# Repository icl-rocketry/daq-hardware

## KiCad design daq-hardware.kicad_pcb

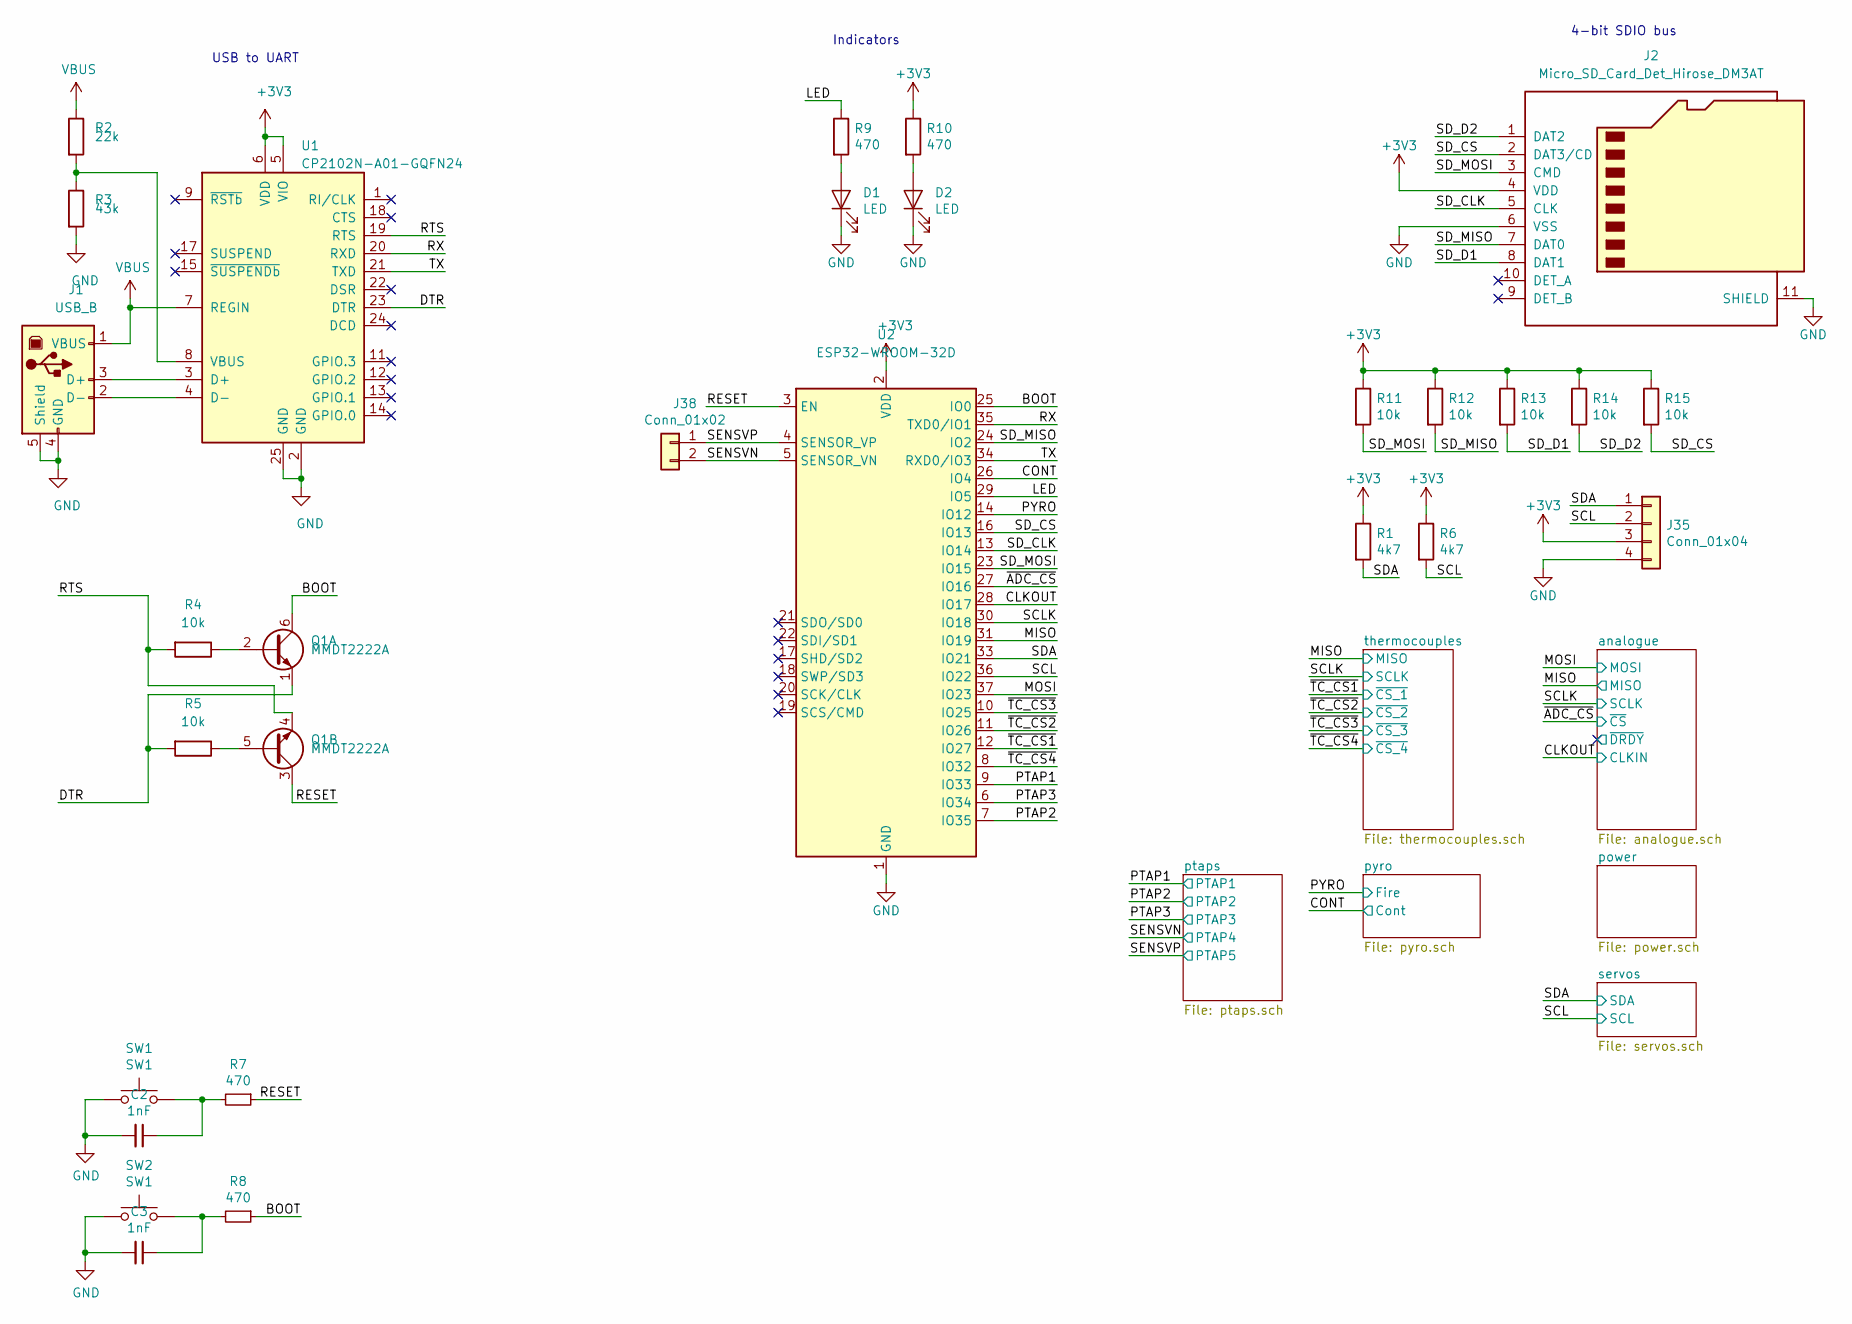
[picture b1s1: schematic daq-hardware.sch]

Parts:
C2, C3: 1nF; C_0603_1608Metric
D1, D2: LED; LED_0603_1608Metric_Castellated
J1: USB_B; USB_B_OST_USB-B1HSxx_Horizontal
J2: Micro_SD_Card_Det_Hirose_DM3AT; microSD_HC_Hirose_DM3AT-SF-PEJM5
J35: Conn_01x04; PinHeader_1x04_P2.54mm_Vertical
J38: Conn_01x02; PinHeader_1x02_P2.54mm_Vertical
Q1: MMDT2222A; SOT-363_SC-70-6
R1, R6: 4k7; R_0603_1608Metric
R2: 22k; R_0603_1608Metric
R3: 43k; R_0603_1608Metric
R4, R5, R11, R12, R13, R14, R15: 10k; R_0603_1608Metric
R7, R8, R9, R10: 470; R_0603_1608Metric
SW1, SW2: SW1; SW_Push_1P1T_NO_CK_KMR2
U1: CP2102N-A01-GQFN24; QFN-24-1EP_4x4mm_P0.5mm_EP2.6x2.6mm_ThermalVias
U2: ESP32-WROOM-32D; ESP32-WROOM-32U

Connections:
+3V3: J2.4 (VDD), J35.3, R1.1, R6.1, R10.1, R11.1, R12.1, R13.1, R14.1, R15.1, U1.5 (VIO), U1.6 (VDD), U2.2 (VDD); also elsewhere on the board
/BOOT: Q1.6 (C1), R8.1, U2.25 (IO0); also elsewhere on the board
/CLKOUT: U2.28 (IO17); also elsewhere on the board
/CONT: U2.26 (IO4); also elsewhere on the board
/DTR: Q1.1 (E1), R5.2, U1.23 (DTR)
/LED: R9.1, U2.29 (IO5); also elsewhere on the board
/MISO: U2.31 (IO19); also elsewhere on the board
/MOSI: U2.37 (IO23); also elsewhere on the board
/PTAP1: U2.9 (IO33); also elsewhere on the board
/PTAP2: U2.7 (IO35); also elsewhere on the board
/PTAP3: U2.6 (IO34); also elsewhere on the board
/PYRO: U2.14 (IO12); also elsewhere on the board
/RESET: Q1.3 (C2), R7.1, U2.3 (EN); also elsewhere on the board
/RTS: Q1.4 (E2), R4.2, U1.19 (RTS)
/RX: U1.20 (RXD), U2.35 (TXD0/IO1); also elsewhere on the board
/SCL: J35.2, R6.2, U2.36 (IO22); also elsewhere on the board
/SCLK: U2.30 (IO18); also elsewhere on the board
/SDA: J35.1, R1.2, U2.33 (IO21); also elsewhere on the board
/SD_CLK: J2.5 (CLK), U2.13 (IO14); also elsewhere on the board
/SD_CS: J2.2 (DAT3/CD), R15.2, U2.16 (IO13); also elsewhere on the board
/SD_D1: J2.8 (DAT1), R13.2
/SD_D2: J2.1 (DAT2), R14.2
/SD_MISO: J2.7 (DAT0), R12.2, U2.24 (IO2); also elsewhere on the board
/SD_MOSI: J2.3 (CMD), R11.2, U2.23 (IO15); also elsewhere on the board
/SENSVN: J38.2, U2.5 (SENSOR_VN); also elsewhere on the board
/SENSVP: J38.1, U2.4 (SENSOR_VP); also elsewhere on the board
/TX: U1.21 (TXD), U2.34 (RXD0/IO3); also elsewhere on the board
/~ADC_CS: U2.27 (IO16); also elsewhere on the board
/~TC_CS1: U2.12 (IO27); also elsewhere on the board
/~TC_CS2: U2.11 (IO26); also elsewhere on the board
/~TC_CS3: U2.10 (IO25); also elsewhere on the board
/~TC_CS4: U2.8 (IO32); also elsewhere on the board
GND: C2.2, C3.2, D1.1 (K), D2.1 (K), J1.4 (GND), J1.5 (Shield), J2.6 (VSS), J2.11 (SHIELD), J35.4, R3.2, SW1.1, SW2.1, U1.2 (GND), U1.25 (GND), U2.1 (GND), U2.15 (GND), U2.38 (GND); also elsewhere on the board
unnamed: C2.1, R7.2, SW1.2
unnamed: C3.1, R8.2, SW2.2
unnamed: D1.2 (A), R9.2
unnamed: D2.2 (A), R10.2
unnamed: J1.2 (D-), U1.4 (D-)
unnamed: J1.3 (D+), U1.3 (D+)
unnamed: Q1.2 (B1), R4.1
unnamed: Q1.5 (B2), R5.1
unnamed: R2.2, R3.1, U1.8 (VBUS)
unnamed 113: U2.17 (SHD/SD2); also elsewhere on the board
unnamed 114: U2.18 (SWP/SD3); also elsewhere on the board
unnamed 115: U2.19 (SCS/CMD); also elsewhere on the board
unnamed 116: U2.20 (SCK/CLK); also elsewhere on the board
unnamed 117: U2.21 (SDO/SD0); also elsewhere on the board
unnamed 118: U2.22 (SDI/SD1); also elsewhere on the board
unnamed 119: U2.32 (NC); also elsewhere on the board
VBUS: J1.1 (VBUS), R2.1, U1.7 (REGIN); also elsewhere on the board

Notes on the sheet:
4-bit SDIO bus
USB to UART
Indicators

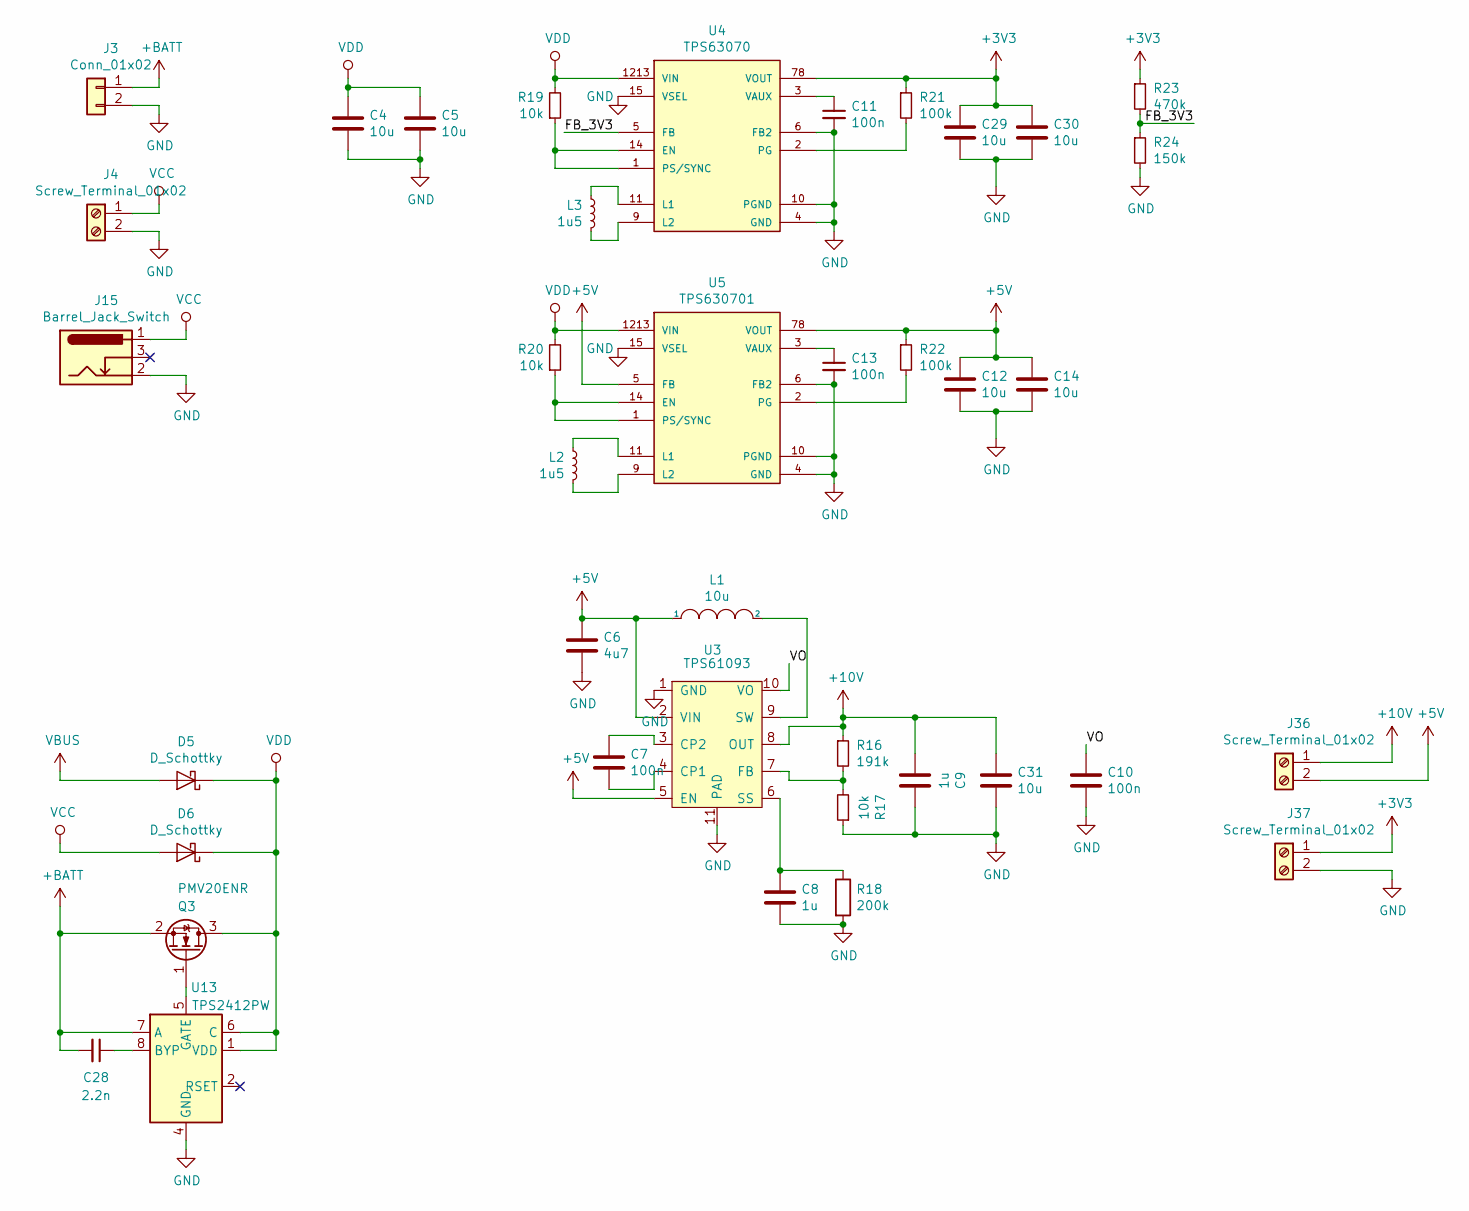
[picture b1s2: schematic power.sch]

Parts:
C4, C5, C12, C14, C29, C30, C31: 10u; CP_Elec_4x5.4
C6: 4u7; C_0603_1608Metric
C7, C10, C11, C13: 100n; C_0603_1608Metric
C8, C9: 1u; C_0603_1608Metric
C28: 2.2n; C_0603_1608Metric
D5, D6: D_Schottky; D_SOD-123F
J3: Conn_01x02; JST_PH_S2B-PH-K_1x02_P2.00mm_Horizontal
J4, J36, J37: Screw_Terminal_01x02; TerminalBlock_Phoenix_MPT-2.54mm_2pol
J15: Barrel_Jack_Switch; BarrelJack_Wuerth_6941xx301002
L1: 10u; L_Taiyo-Yuden_NR-30xx
L2, L3: 1u5; L_Taiyo-Yuden_NR-30xx
Q3: PMV20ENR; SOT-23
R16: 191k; R_0603_1608Metric
R17, R19, R20: 10k; R_0603_1608Metric
R18: 200k; R_0603_1608Metric
R21, R22: 100k; R_0603_1608Metric
R23: 470k; R_0603_1608Metric
R24: 150k; R_0603_1608Metric
U3: TPS61093; Texas_S-PWSON-N10_ThermalVias
U4: TPS63070; Texas_PowerVFQFN_15
U5: TPS630701; Texas_PowerVFQFN_15
U13: TPS2412PW; TSSOP-8_4.4x3mm_P0.65mm

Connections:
+3V3: C29.1, C30.1, J37.1, R21.1, R23.1, U4.78 (VOUT); also elsewhere on the board
+5V: C6.1, C12.1, C14.1, J36.2, L1.1, R22.1, U3.2 (VIN), U3.5 (EN), U5.5 (FB), U5.78 (VOUT); also elsewhere on the board
+10V: C9.2, C31.1, J36.1, R16.1, U3.8 (OUT)
+BATT: C28.2, J3.1, Q3.2 (S), U13.7 (A)
/power/FB_3V3: R23.2, R24.1, U4.5 (FB)
/power/VO: C10.1, U3.10 (VO)
GND: C4.2, C5.2, C6.2, C8.2, C9.1, C10.2, C11.2, C12.2, C13.2, C14.2, C29.2, C30.2, C31.2, J3.2, J4.2, J15.2, J37.2, R17.1, R18.2, R24.2, U3.1 (GND), U3.11 (PAD), U4.4 (GND), U4.6 (FB2), U4.10 (PGND), U4.15 (VSEL), U5.4 (GND), U5.6 (FB2), U5.10 (PGND), U5.15 (VSEL), U13.3 (GND), U13.4 (GND); also elsewhere on the board
unnamed: C7.1, U3.3 (CP2)
unnamed: C7.2, U3.4 (CP1)
unnamed: C8.1, R18.1, U3.6 (SS)
unnamed: C11.1, U4.3 (VAUX)
unnamed: C13.1, U5.3 (VAUX)
unnamed: C28.1, U13.8 (BYP)
unnamed: L1.2, U3.9 (SW)
unnamed: L2.1, U5.9 (L2)
unnamed: L2.2, U5.11 (L1)
unnamed: L3.1, U4.9 (L2)
unnamed: L3.2, U4.11 (L1)
unnamed: Q3.1 (G), U13.5 (GATE)
unnamed: R16.2, R17.2, U3.7 (FB)
unnamed: R19.1, U4.1 (PS/SYNC), U4.14 (EN)
unnamed: R20.1, U5.1 (PS/SYNC), U5.14 (EN)
unnamed: R21.2, U4.2 (PG)
unnamed: R22.2, U5.2 (PG)
VBUS: D5.2 (A); also elsewhere on the board
VCC: D6.2 (A), J4.1, J15.1
VDD: C4.1, C5.1, D5.1 (K), D6.1 (K), Q3.3 (D), R19.2, R20.2, U4.1213 (VIN), U5.1213 (VIN), U13.1 (VDD), U13.6 (C)

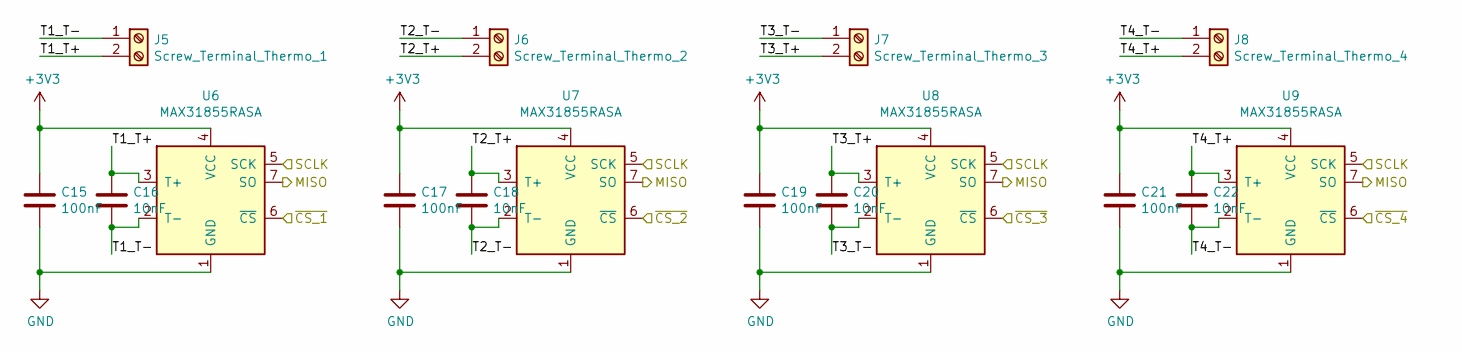
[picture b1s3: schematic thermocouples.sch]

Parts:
C15, C17, C19, C21: 100nF; C_0603_1608Metric
C16, C18, C20, C22: 10nF; C_0603_1608Metric
J5: Screw_Terminal_Thermo_1; TerminalBlock_Phoenix_MPT-2.54mm_2pol
J6: Screw_Terminal_Thermo_2; TerminalBlock_Phoenix_MPT-2.54mm_2pol
J7: Screw_Terminal_Thermo_3; TerminalBlock_Phoenix_MPT-2.54mm_2pol
J8: Screw_Terminal_Thermo_4; TerminalBlock_Phoenix_MPT-2.54mm_2pol
U6, U7, U8, U9: MAX31855RASA; SOIC-8_3.9x4.9mm_P1.27mm

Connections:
+3V3: C15.1, C17.1, C19.1, C21.1, U6.4 (VCC), U7.4 (VCC), U8.4 (VCC), U9.4 (VCC); also elsewhere on the board
/MISO: U6.7 (SO), U7.7 (SO), U8.7 (SO), U9.7 (SO); also elsewhere on the board
/SCLK: U6.5 (SCK), U7.5 (SCK), U8.5 (SCK), U9.5 (SCK); also elsewhere on the board
/thermocouples/T1_T+: C16.1, J5.2, U6.3 (T+)
/thermocouples/T1_T-: C16.2, J5.1, U6.2 (T-)
/thermocouples/T2_T+: C18.1, J6.2, U7.3 (T+)
/thermocouples/T2_T-: C18.2, J6.1, U7.2 (T-)
/thermocouples/T3_T+: C20.1, J7.2, U8.3 (T+)
/thermocouples/T3_T-: C20.2, J7.1, U8.2 (T-)
/thermocouples/T4_T+: C22.1, J8.2, U9.3 (T+)
/thermocouples/T4_T-: C22.2, J8.1, U9.2 (T-)
/~TC_CS1: U6.6 (~CS~); also elsewhere on the board
/~TC_CS2: U7.6 (~CS~); also elsewhere on the board
/~TC_CS3: U8.6 (~CS~); also elsewhere on the board
/~TC_CS4: U9.6 (~CS~); also elsewhere on the board
GND: C15.2, C17.2, C19.2, C21.2, U6.1 (GND), U7.1 (GND), U8.1 (GND), U9.1 (GND); also elsewhere on the board

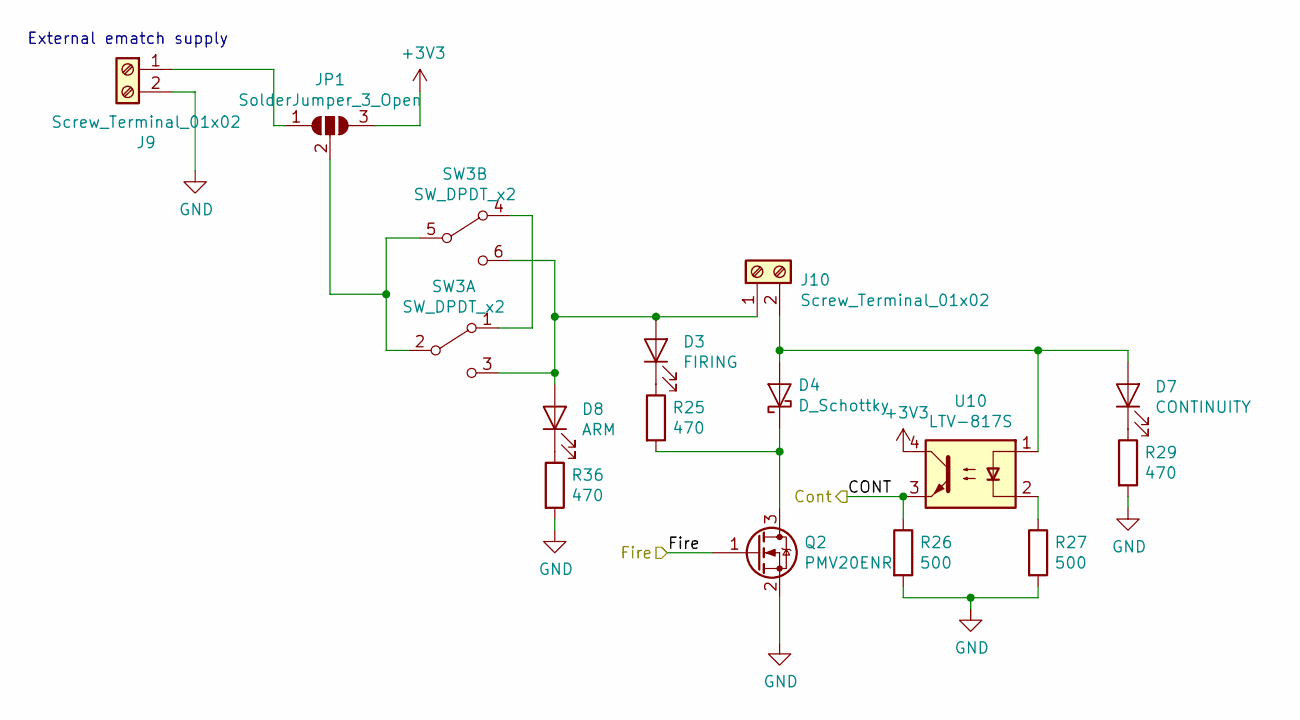
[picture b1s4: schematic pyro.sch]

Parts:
D3: FIRING; LED_0603_1608Metric_Castellated
D4: D_Schottky; D_SOD-123F
D7: CONTINUITY; LED_0603_1608Metric_Castellated
D8: ARM; LED_0603_1608Metric_Castellated
J9, J10: Screw_Terminal_01x02; TerminalBlock_Phoenix_MPT-0,5-2-2.54_1x02_P2.54mm_Horizontal
JP1: SolderJumper_3_Open; SolderJumper-3_P1.3mm_Open_RoundedPad1.0x1.5mm_NumberLabels
Q2: PMV20ENR; SOT-23
R25, R29, R36: 470; R_0603_1608Metric
R26, R27: 500; R_0603_1608Metric
SW3: SW_DPDT_x2; SW_CuK_JS202011AQN_DPDT_Angled
U10: LTV-817S; SMDIP-4_W9.53mm

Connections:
+3V3: JP1.3 (B), U10.4; also elsewhere on the board
/CONT: R26.1, U10.3; also elsewhere on the board
/PYRO: Q2.1 (G); also elsewhere on the board
GND: J9.2, Q2.2 (S), R26.2, R27.2, R29.2, R36.2; also elsewhere on the board
unnamed: D3.1 (K), R25.1
unnamed: D3.2 (A), D8.2 (A), J10.1, SW3.3 (C), SW3.6 (C)
unnamed: D4.1 (K), Q2.3 (D), R25.2
unnamed: D4.2 (A), D7.2 (A), J10.2, U10.1
unnamed: D7.1 (K), R29.1
unnamed: D8.1 (K), R36.1
unnamed: J9.1, JP1.1 (A)
unnamed: JP1.2 (C), SW3.2 (B), SW3.5 (B)
unnamed: R27.1, U10.2
unnamed: SW3.1 (A), SW3.4 (A)

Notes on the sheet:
External ematch supply

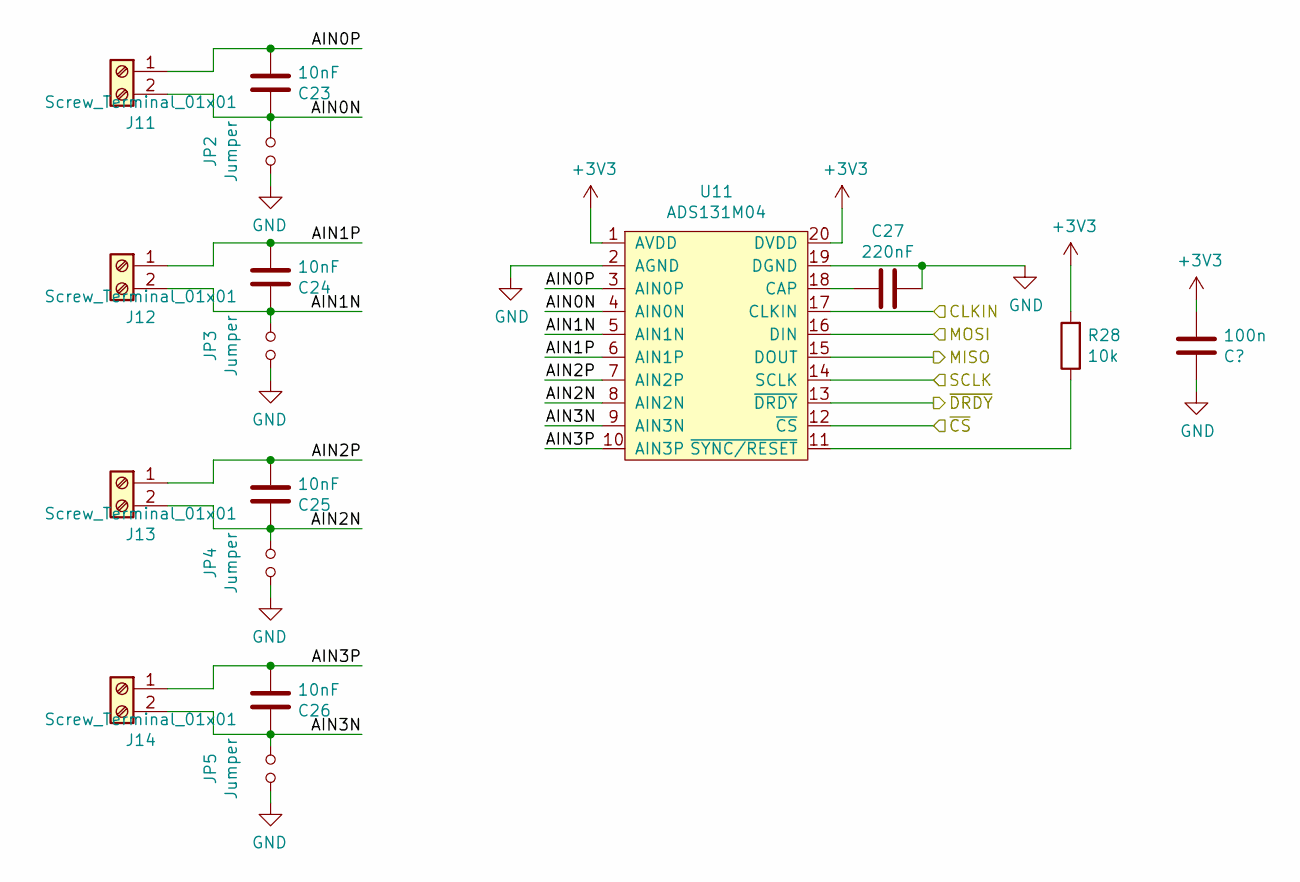
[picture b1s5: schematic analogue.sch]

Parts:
C23, C24, C25, C26: 10nF; C_0603_1608Metric
C27: 220nF; C_0603_1608Metric_Pad1.05x0.95mm_HandSolder
J11, J12, J13, J14: Screw_Terminal_01x01; TerminalBlock_Phoenix_MPT-2.54mm_2pol
JP2, JP3, JP4, JP5: Jumper; PinHeader_1x02_P2.54mm_Vertical
R28: 10k; R_0603_1608Metric
U11: ADS131M04; TSSOP-20_4.4x6.5mm_Pitch0.65mm

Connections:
+3V3: R28.2, U11.1 (AVDD), U11.20 (DVDD); also elsewhere on the board
/CLKOUT: U11.17 (CLKIN); also elsewhere on the board
/MISO: U11.15 (DOUT); also elsewhere on the board
/MOSI: U11.16 (DIN); also elsewhere on the board
/SCLK: U11.14 (SCLK); also elsewhere on the board
/analogue/AIN0N: C23.1, J11.2, JP2.1, U11.4 (AIN0N)
/analogue/AIN0P: C23.2, J11.1, U11.3 (AIN0P)
/analogue/AIN1N: C24.1, J12.2, JP3.1, U11.5 (AIN1N)
/analogue/AIN1P: C24.2, J12.1, U11.6 (AIN1P)
/analogue/AIN2N: C25.1, J13.2, JP4.1, U11.8 (AIN2N)
/analogue/AIN2P: C25.2, J13.1, U11.7 (AIN2P)
/analogue/AIN3N: C26.1, J14.2, JP5.1, U11.9 (AIN3N)
/analogue/AIN3P: C26.2, J14.1, U11.10 (AIN3P)
/~ADC_CS: U11.12 (~CS); also elsewhere on the board
GND: C27.1, JP2.2, JP3.2, JP4.2, JP5.2, U11.2 (AGND), U11.19 (DGND); also elsewhere on the board
unnamed: C27.2, U11.18 (CAP)
unnamed: R28.1, U11.11 (~SYNC/RESET)

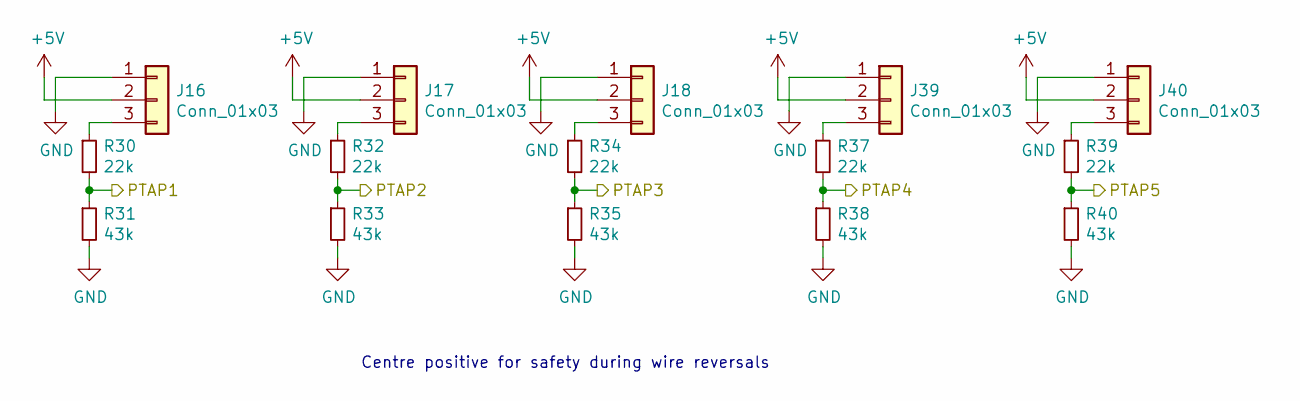
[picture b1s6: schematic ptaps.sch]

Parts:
J16, J17, J18, J39, J40: Conn_01x03; JST_XH_B3B-XH-A_1x03_P2.50mm_Vertical
R30, R32, R34, R37, R39: 22k; R_0603_1608Metric
R31, R33, R35, R38, R40: 43k; R_0603_1608Metric

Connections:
+5V: J16.2, J17.2, J18.2, J39.2, J40.2; also elsewhere on the board
/PTAP1: R30.2, R31.1; also elsewhere on the board
/PTAP2: R32.2, R33.1; also elsewhere on the board
/PTAP3: R34.2, R35.1; also elsewhere on the board
/SENSVN: R37.2, R38.1; also elsewhere on the board
/SENSVP: R39.2, R40.1; also elsewhere on the board
GND: J16.1, J17.1, J18.1, J39.1, J40.1, R31.2, R33.2, R35.2, R38.2, R40.2; also elsewhere on the board
unnamed: J16.3, R30.1
unnamed: J17.3, R32.1
unnamed: J18.3, R34.1
unnamed: J39.3, R37.1
unnamed: J40.3, R39.1

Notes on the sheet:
Centre positive for safety during wire reversals

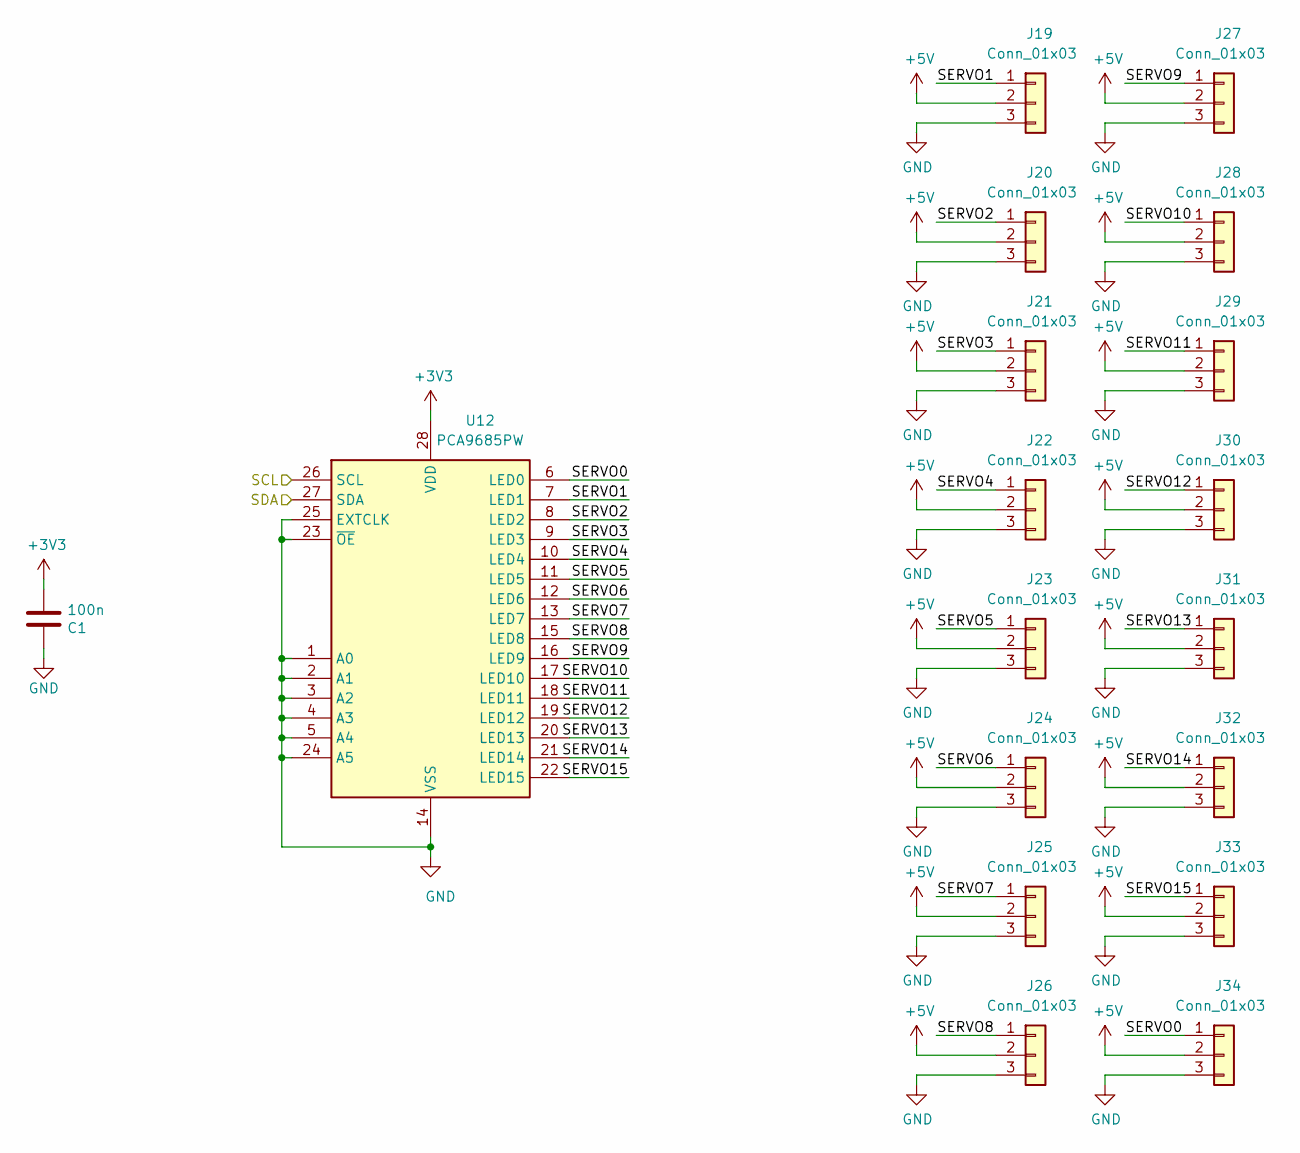
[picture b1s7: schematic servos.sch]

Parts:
C1: 100n; C_0603_1608Metric
J19, J20, J21, J22, J23, J24, J25, J26, J27, J28, J29, J30, J31, J32, J33, J34: Conn_01x03; PinHeader_1x03_P2.54mm_Vertical
U12: PCA9685PW; TSSOP-28_4.4x9.7mm_P0.65mm

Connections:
+3V3: C1.2, U12.28 (VDD); also elsewhere on the board
+5V: J19.2, J20.2, J21.2, J22.2, J23.2, J24.2, J25.2, J26.2, J27.2, J28.2, J29.2, J30.2, J31.2, J32.2, J33.2, J34.2; also elsewhere on the board
/SCL: U12.26 (SCL); also elsewhere on the board
/SDA: U12.27 (SDA); also elsewhere on the board
/servos/SERVO0: J34.1, U12.6 (LED0)
/servos/SERVO1: J19.1, U12.7 (LED1)
/servos/SERVO2: J20.1, U12.8 (LED2)
/servos/SERVO3: J21.1, U12.9 (LED3)
/servos/SERVO4: J22.1, U12.10 (LED4)
/servos/SERVO5: J23.1, U12.11 (LED5)
/servos/SERVO6: J24.1, U12.12 (LED6)
/servos/SERVO7: J25.1, U12.13 (LED7)
/servos/SERVO8: J26.1, U12.15 (LED8)
/servos/SERVO9: J27.1, U12.16 (LED9)
/servos/SERVO10: J28.1, U12.17 (LED10)
/servos/SERVO11: J29.1, U12.18 (LED11)
/servos/SERVO12: J30.1, U12.19 (LED12)
/servos/SERVO13: J31.1, U12.20 (LED13)
/servos/SERVO14: J32.1, U12.21 (LED14)
/servos/SERVO15: J33.1, U12.22 (LED15)
GND: C1.1, J19.3, J20.3, J21.3, J22.3, J23.3, J24.3, J25.3, J26.3, J27.3, J28.3, J29.3, J30.3, J31.3, J32.3, J33.3, J34.3, U12.1 (A0), U12.2 (A1), U12.3 (A2), U12.4 (A3), U12.5 (A4), U12.14 (VSS), U12.23 (~OE), U12.24 (A5), U12.25 (EXTCLK); also elsewhere on the board

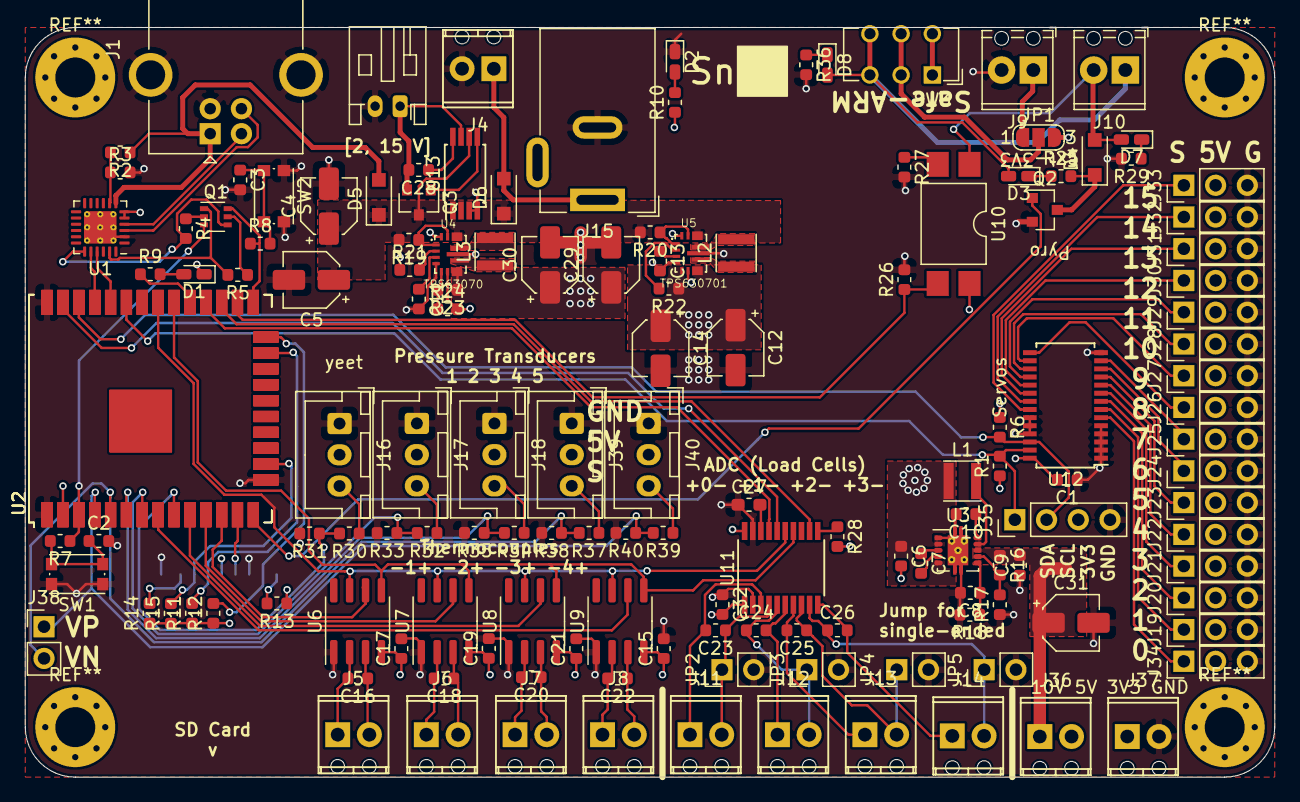
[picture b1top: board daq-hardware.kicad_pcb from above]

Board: 4 copper layers, 100.0 x 60.0 mm, 149 parts (1 on the bottom side), 123 nets.

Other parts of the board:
C32: 100n; C_0603_1608Metric
U2#2, U2#3: ESP32-WROOM-32D; ESP32-WROOM-32U

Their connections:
+3V3: C32.2, U2#2.2, U2#3.2; also elsewhere on the board
/BOOT: U2#2.25, U2#3.25; also elsewhere on the board
/CLKOUT: U2#2.28, U2#3.28; also elsewhere on the board
/CONT: U2#2.26, U2#3.26; also elsewhere on the board
/LED: U2#2.29, U2#3.29; also elsewhere on the board
/MISO: U2#2.31, U2#3.31; also elsewhere on the board
/MOSI: U2#2.37, U2#3.37; also elsewhere on the board
/PTAP1: U2#2.9, U2#3.9; also elsewhere on the board
/PTAP2: U2#2.7, U2#3.7; also elsewhere on the board
/PTAP3: U2#2.6, U2#3.6; also elsewhere on the board
/PYRO: U2#2.14, U2#3.14; also elsewhere on the board
/RESET: U2#2.3, U2#3.3; also elsewhere on the board
/RX: U2#2.35, U2#3.35; also elsewhere on the board
/SCL: U2#2.36, U2#3.36; also elsewhere on the board
/SCLK: U2#2.30, U2#3.30; also elsewhere on the board
/SDA: U2#2.33, U2#3.33; also elsewhere on the board
/SD_CLK: U2#2.13, U2#3.13; also elsewhere on the board
/SD_CS: U2#2.16, U2#3.16; also elsewhere on the board
/SD_MISO: U2#2.24, U2#3.24; also elsewhere on the board
/SD_MOSI: U2#2.23, U2#3.23; also elsewhere on the board
/SENSVN: U2#2.5, U2#3.5; also elsewhere on the board
/SENSVP: U2#2.4, U2#3.4; also elsewhere on the board
/TX: U2#2.34, U2#3.34; also elsewhere on the board
/~ADC_CS: U2#2.27, U2#3.27; also elsewhere on the board
/~TC_CS1: U2#2.12, U2#3.12; also elsewhere on the board
/~TC_CS2: U2#2.11, U2#3.11; also elsewhere on the board
/~TC_CS3: U2#2.10, U2#3.10; also elsewhere on the board
/~TC_CS4: U2#2.8, U2#3.8; also elsewhere on the board
GND: C32.1, U2#2.1, U2#2.15, U2#2.38, U2#3.1, U2#3.15, U2#3.38; also elsewhere on the board
unnamed 113: U2#2.17, U2#3.17; also elsewhere on the board
unnamed 114: U2#2.18, U2#3.18; also elsewhere on the board
unnamed 115: U2#2.19, U2#3.19; also elsewhere on the board
unnamed 116: U2#2.20, U2#3.20; also elsewhere on the board
unnamed 117: U2#2.21, U2#3.21; also elsewhere on the board
unnamed 118: U2#2.22, U2#3.22; also elsewhere on the board
unnamed 119: U2#2.32, U2#3.32; also elsewhere on the board

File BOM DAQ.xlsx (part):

Id | Designator | Package | Quantity | Designation | Supplier and ref | Digikey Part Nr | Unit Pricing | url
1 | C32,C13,C11,C1,C10,C7 | C_0603_1608Metric | 6 | 100n | Samsung Electro-Mech - CL10B104KB8NNNC | 1276-1000-1-ND | $0.02600 @ qty 10 | https://www.digikey.com/product-detail/en/samsung-electro-me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
2 | J40,J39,J18,J17,J16 | JST_XH_B3B-XH-A_1x03_P2.50mm_Vertical | 5 | Conn_01x03
3 | R40,R38,R35,R33,R31,R3 | R_0603_1608Metric | 6 | 43k | Yageo - RC0603FR-0743KL | 311-43.0KHRCT-ND | 0.1 | https://www.digikey.com/product-detail/en/yageo/RC0603FR-074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
4 | R39,R37,R34,R32,R30,R2 | R_0603_1608Metric | 6 | 22k | TE - CRGCQ0603F22K | A129704CT-ND | 0.1 | https://www.digikey.com/product-detail/en/te-connectivity-pa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
5 | J38 | PinHeader_1x02_P2.54mm_Vertical | 1 | Conn_01x02
6 | D2,D1 | LED_0603_1608Metric_Castellated | 2 | LED
7 | R36,R29,R10,R9,R8,R7,R25 | R_0603_1608Metric | 7 | 470 | TE - CRGCQ0603F470R | A129684CT-ND | 0.1 | https://www.digikey.com/product-detail/en/te-connectivity-pa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
8 | D8 | LED_0603_1608Metric_Castellated | 1 | ARM
9 | SW3 | SW_CuK_JS202011AQN_DPDT_Angled | 1 | SW_DPDT_x2 | C&K - JS202011AQN | 401-2000-ND | $0.43 | https://www.digikey.com/products/en?keywords=JS202011AQN
10 | C31,C30,C29,C14,C12,C5,C4 | CP_Elec_4x5.4 | 7 | 10u | Panasonic Elec - ECE-A1HKS100I | P19589CT-ND | $0.03400 @ qty 10 | https://www.digikey.com/product-detail/en/panasonic-electron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
11 | J37,J36,J4 | TerminalBlock_Phoenix_MPT-2.54mm_2pol | 3 | Screw_Terminal_01x02 | On Shore Tech - OSTVN02A150 | ED10561-ND | $0.91 | https://www.digikey.com/product-detail/en/on-shore-technolog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
12 | C27 | C_0603_1608Metric_Pad1.05x0.95mm_HandSolder | 1 | 220nF | Samsung Electro-Mech - CL10B222KB8NCNC | 1276-1989-1-ND | $0.02900 @ qty 10 | https://www.digikey.com/product-detail/en/samsung-electro-me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
13 | R20,R19,R12,R15,R14,R13,R11,R28,R17,R5,R4 | R_0603_1608Metric | 11 | 10k | TE -CRGCQ0603F10K | A129700CT-ND | 0.1 | https://www.digikey.com/product-detail/en/te-connectivity-pa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
14 | U4 | Texas_PowerVFQFN_15 | 1 | TPS63070 | Texas Instruments - TPS63070RNMR | 296-44874-1-ND | $2.67 | https://www.digikey.com/product-detail/en/texas-instruments/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
15 | R24 | R_0603_1608Metric | 1 | 150k | TE - CRGCQ0603F150K | A129714CT-ND | 0.1 | https://www.digikey.com/product-detail/en/te-connectivity-pa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
16 | R23 | R_0603_1608Metric | 1 | 470k | TE - CRGCQ0603F470K | A129720CT-ND | 0.1 | https://www.digikey.com/product-detail/en/te-connectivity-pa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
17 | U5 | Texas_PowerVFQFN_15 | 1 | TPS630701 | Texas Instruments - TPS630701RNMR | 296-47298-1-ND | $2.67 | https://www.digikey.com/product-detail/en/texas-instruments/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
18 | R22,R21 | R_0603_1608Metric | 2 | 100k | TE - CRGCQ0603F100K | A129712CT-ND | 0.1 | https://www.digikey.com/product-detail/en/te-connectivity-pa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
19 | L3,L2 | L_Taiyo-Yuden_NR-30xx | 2 | 1u5 | Taiyo Yuden - NR3015T1R5N | 587-2617-1-ND | $0.41 | https://www.digikey.com/product-detail/en/taiyo-yuden/NR3015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
20 | J35 | PinHeader_1x04_P2.54mm_Vertical | 1 | Conn_01x04
21 | JP3,JP5,JP4,JP2 | PinHeader_1x02_P2.54mm_Vertical | 4 | Jumper
22 | R6,R1 | R_0603_1608Metric | 2 | 4k7 | TE - CRGCQ0603F4K7 | A129696CT-ND | 0.1 | https://www.digikey.com/product-detail/en/te-connectivity-pa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
23 | J34,J33,J32,J31,J30,J29,J28,J27,J26,J25,J24,J23,J22,J21,J20,J19 | PinHeader_1x03_P2.54mm_Vertical | 16 | Conn_01x03
24 | U12 | TSSOP-28_4.4x9.7mm_P0.65mm | 1 | PCA9685PW | NXP USA - PCA9685PW,118 | 568-11925-1-ND | $2.33 | https://www.digikey.com/product-detail/en/nxp-usa-inc/PCA968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
25 | U2,U2,U2 | ESP32-WROOM-32U | 3 | ESP32-WROOM-32D | Expressif Systems - ESP32-WROOM-32D | 1904-1023-1-ND | $3.8 | https://www.digikey.com/product-detail/en/espressif-systems/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
26 | SW2,SW1 | SW_Push_1P1T_NO_CK_KMR2 | 2 | SW1 | C&K - K12SCS1.55NOLFTX | CKN10790CT-ND | $2.33 | https://www.digikey.com/product-detail/en/c-k/K12SCS1.55NOLF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
27 | D7 | LED_0603_1608Metric_Castellated | 1 | CONTINUITY
28 | D3 | LED_0603_1608Metric_Castellated | 1 | FIRING
29 | C3,C2 | C_0603_1608Metric | 2 | 1nF | Wurth - 885012206083 | 732-8001-1-ND | $0.01700 @ qty 10 | https://www.digikey.com/product-detail/en/w-rth-elektronik/8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
30 | D4,D6,D5 | D_SOD-123F | 3 | D_Schottky
31 | Q3,Q2 | SOT-23 | 2 | PMV20ENR | Nexperia USA - PMV20ENR | 1727-2301-1-ND | $0.39 | https://www.digikey.com/products/en/discrete-semiconductor-p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
32 | C28 | C_0603_1608Metric | 1 | 2.2n | Wurth - 885012206085 | 732-8003-1-ND | $0.01900 @ qty 10 | https://www.digikey.com/product-detail/en/w-rth-elektronik/8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
33 | U13 | TSSOP-8_4.4x3mm_P0.65mm | 1 | TPS2412PW | Texas Instruments - TPS2412PWR | 296-39371-1-ND | $2.88 | https://www.digikey.com/products/en/integrated-circuits-ics/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
34 | J15 | BarrelJack_Wuerth_6941xx301002 | 1 | Barrel_Jack_Switch
35 | J1 | USB_B_OST_USB-B1HSxx_Horizontal | 1 | USB_B | Kycon - KUSBX-SMTBS1NBTR | 2092-KUSBX-SMTBS1NBCT-ND | $1.50 | https://www.digikey.com/product-detail/en/kycon-inc/KUSBX-SM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
36 | JP1 | SolderJumper-3_P1.3mm_Open_RoundedPad1.0x1.5mm_NumberLabels | 1 | SolderJumper_3_Open
37 | J14,J13,J12,J11 | TerminalBlock_Phoenix_MPT-2.54mm_2pol | 4 | Screw_Terminal_01x01
38 | J8 | TerminalBlock_Phoenix_MPT-2.54mm_2pol | 1 | Screw_Terminal_Thermo_4
39 | J7 | TerminalBlock_Phoenix_MPT-2.54mm_2pol | 1 | Screw_Terminal_Thermo_3
40 | J6 | TerminalBlock_Phoenix_MPT-2.54mm_2pol | 1 | Screw_Terminal_Thermo_2
41 | J5 | TerminalBlock_Phoenix_MPT-2.54mm_2pol | 1 | Screw_Terminal_Thermo_1
42 | C15,C19,C17,C21 | C_0603_1608Metric | 4 | 100nF | Samsung Electro-Mech - CL10B104KB8NNNC | 1276-1000-1-ND | $0.02600 @ qty 10 | https://www.digikey.com/product-detail/en/samsung-electro-me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
43 | J2 | microSD_HC_Hirose_DM3AT-SF-PEJM5 | 1 | Micro_SD_Card_Det_Hirose_DM3AT | Hirose Electric Co Ltd - M3AT-SF-PEJM5 | HR1964CT-ND | $2.67 | https://www.digikey.com/product-detail/en/hirose-electric-co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
44 | U1 | QFN-24-1EP_4x4mm_P0.5mm_EP2.6x2.6mm_ThermalVias | 1 | CP2102N-A01-GQFN24 | Silicon Labs - CP2102N-A01-GQFN24R | 336-4737-1-ND | $1.35 | https://www.digikey.com/products/en/integrated-circuits-ics/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
45 | U11 | TSSOP-20_4.4x6.5mm_Pitch0.65mm | 1 | ADS131M04 | Texas Instruments - ADS131M04IPWT | 296-ADS131M04IPWTCT-ND | $6.22 | https://www.digikey.com/products/en/integrated-circuits-ics/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
46 | U3 | Texas_S-PWSON-N10_ThermalVias | 1 | TPS61093 | Texas Instruments - TPS61093DSKR | 296-39430-1-ND | $2.67 | https://www.digikey.com/product-detail/en/texas-instruments/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
47 | R18 | R_0603_1608Metric | 1 | 200k | Panasonic Electronics - ERJ-3EKF2003V | P200KHCT-ND | 0.1 | https://www.digikey.com/product-detail/en/panasonic-electron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
48 | R16 | R_0603_1608Metric | 1 | 191k | Panasonic Electronics - ERJ-3EKF1913V | P191KHCT-ND | 0.1 | https://www.digikey.com/product-detail/en/panasonic-electron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
49 | L1 | L_Taiyo-Yuden_NR-30xx | 1 | 10u | Taiyo Yuden - NR3015T100M | 587-1650-1-ND | $0.35 | https://www.digikey.com/product-detail/en/taiyo-yuden/NR3015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
50 | C26,C25,C24,C23,C22,C20,C18,C16 | C_0603_1608Metric | 8 | 10nF | Wurth - 885012206089 | 732-8007-1-ND | $0.01900 @ qty 10 | https://www.digikey.com/product-detail/en/w-rth-elektronik/8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
51 | C9,C8 | C_0603_1608Metric | 2 | 1u | Samsung Electro-Mech - CL10A105KQ8NNNC | 1276-1036-1-ND | $0.03300 @ qty 10 | https://www.digikey.com/product-detail/en/samsung-electro-me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
52 | C6 | C_0603_1608Metric | 1 | 4u7 | Samsung Electro-Mech - CL10A475KQ8NNNC | 1276-1045-1-ND | $0.05500 @ qty 10 | https://www.digikey.com/product-detail/en/samsung-electro-me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
53 | U10 | SMDIP-4_W9.53mm | 1 | LTV-817S | Lite-On LTV-817S-TA1 | 160-1893-1-ND | 0.49 | https://www.digikey.com/product-detail/en/lite-on-inc/LTV-81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
54 | R27,R26 | R_0603_1608Metric | 2 | 500 | Panasonic Electronics - ERJ-3EKF4990V | P499HCT-ND | $0.10 | https://www.digikey.com/product-detail/en/panasonic-electron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
55 | J10,J9 | TerminalBlock_Phoenix_MPT-0,5-2-2.54_1x02_P2.54mm_Horizontal | 2 | Screw_Terminal_01x02 | On Shore Tech - OSTVN02A150 | ED10561-ND | $0.91 | https://www.digikey.com/product-detail/en/on-shore-technolog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
